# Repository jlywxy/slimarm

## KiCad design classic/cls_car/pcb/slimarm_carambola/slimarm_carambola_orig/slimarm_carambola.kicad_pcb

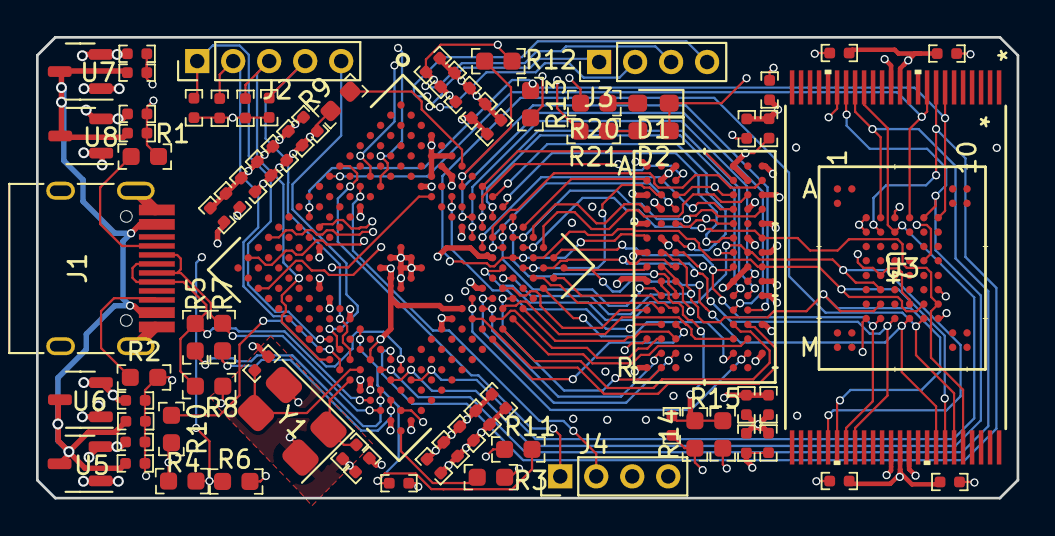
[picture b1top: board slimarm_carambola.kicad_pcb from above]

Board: 4 copper layers, 54.5 x 25.6 mm, 77 parts (0 on the bottom side), 84 nets.

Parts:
C1, C2, C3, C4, C5, C6, C7, C8, C9, C10, C11, C12, C13, C14, C15, C16, C17, C18, C19, C20, C21, C22, C23, C24, C25, C27, C28, C29, C30: 100nF; 0402
C26, C31, C32, C33, C34, C35, C36, C37, C38, C39, C40, C41: 22pF; 0402
D1, D2: LED; LED_0603_1608Metric_Pad1.05x0.95mm_HandSolder
J1: USB_C_Receptacle_USB2.0; USB_TYPEC_Receptacle
J2: Conn_01x05; PinHeader_1x05_P2.00mm_Vertical
J3, J4: Conn_01x04; PinHeader_1x04_P2.00mm_Vertical
R1, R2: 5.1k; 0603
R3: 6.8k; 0603
R4: NC; 0603
R5, R7: 39; 0603
R6: 0; 0603
R8, R10, R11, R14, R15: 1.5k; 0603
R9: 10k; 0603
R12, R13: 470k; 0603
R16, R17, R18, R19: 10k; 0402
R20, R21: 5.6k; 0603
U1: AT91SAM9G25-CU; AT91SAM9G25_JKT
U2: 16bit-DDR2-8bank-FBGA84; BGA84_DDR2
U3: 8bit-NAND-1CE-VFBGA63; VFBGA63_NAND
U4: 8bit-NAND-2CE-TSOP48; TSOP48_NAND
U5, U6, U7, U8: XC6206PxxxMR; SOT-23-3
Y1: Crystal_GND24; Crystal_5032-4P

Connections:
+5V: C33.2, C35.2, C37.2, C39.2, J1.A4 (VBUS), J1.A9 (VBUS), J1.B4 (VBUS), J1.B9 (VBUS), U5.3 (VI), U6.3 (VI), U7.3 (VI), U8.3 (VI)
/1v0_CPUCORE: C12.2, C13.2, C14.2, C15.2, C16.2, C17.2, C18.2, C40.2, U1.H14 (VDDCORE), U1.K8 (VDDCORE), U1.K9 (VDDCORE), U1.R12 (VDDPLLA), U1.T17 (VDDUTMIC), U8.2 (VO)
/1v8_CPUMEM: C9.2, C10.2, C11.2, C36.2, U1.D10 (VDDIOM), U1.D13 (VDDIOM), U1.F14 (VDDIOM), U6.2 (VO)
/1v8_DDR: C19.2, C20.2, C21.2, C22.2, C23.2, C24.2, C25.2, C38.2, U2.A1 (VDD), U2.A9 (VDDQ), U2.C1 (VDDQ), U2.C3 (VDDQ), U2.C7 (VDDQ), U2.C9 (VDDQ), U2.E1 (VDD), U2.E9 (VDDQ), U2.G1 (VDDQ), U2.G3 (VDDQ), U2.G7 (VDDQ), U2.G9 (VDDQ), U2.J1 (VDD), U2.J9 (VDD), U2.M9 (VDD), U2.R1 (VDD), U7.2 (VO)
/3v3: C1.2, C2.2, C3.2, C4.2, C5.2, C6.2, C7.2, C8.2, C27.2, C28.2, C29.2, C30.2, C34.2, J4.3, R4.1, R9.2, R10.2, R11.1, R12.2, R13.2, R15.2, R16.2, R17.2, R18.2, R19.2, U1.A4 (ADVREF), U1.A6 (XIN32), U1.B5 (VDDBU), U1.C6 (VDDANA), U1.H4 (VDDIOP1), U1.J14 (VDDNF), U1.K14 (VDDNF), U1.P7 (VDDIOP0), U1.P9 (BMS), U1.T13 (VDDOSC), U1.U16 (VDDUTMII), U3.C3 (WP#), U3.D3 (VCC2), U3.G4 (VCC2), U3.H8 (VCC), U3.J6 (VCC), U4.12 (Vcc), U4.19 (WP-), U4.37 (Vcc), U5.2 (VO)
/DDR_A0: U1.H15 (A2), U2.M8 (A0)
/DDR_A1: U1.H17 (A3), U2.M3 (A1)
/DDR_A2: U1.G17 (A4), U2.M7 (A2)
/DDR_A3: U1.G16 (A5), U2.N2 (A3)
/DDR_A4: U1.F17 (A6), U2.N8 (A4)
/DDR_A5: U1.E17 (A7), U2.N3 (A5)
/DDR_A6: U1.F16 (A8), U2.N7 (A6)
/DDR_A7: U1.G15 (A9), U2.P2 (A7)
/DDR_A8: U1.G14 (A10), U2.P8 (A8)
/DDR_A9: U1.F15 (A11), U2.P3 (A9)
/DDR_A10: U1.C8 (SDA10), U2.M2 (A10/AP)
/DDR_A11: U1.C17 (A13), U2.P7 (A11)
/DDR_A12: U1.E16 (A14), U2.R2 (A12)
/DDR_BA0: U1.C16 (A16), U2.L2 (BA0)
/DDR_BA1: U1.B17 (A17), U2.L3 (BA1)
/DDR_BA2: U1.E15 (A18), U2.L1 (BA2)
/DDR_CAS: U1.C10 (CAS), U2.L7 (CAS*)
/DDR_CKE: U1.B12 (SDCKE), U2.K2 (DKE)
/DDR_CLK: U1.D11 (SDCK), U2.J8 (CK)
/DDR_CS: R12.1, U1.B8 (NCS1), U2.L8 (CS*)
/DDR_D0: U1.D14 (D0), U2.G8 (DQ0), U3.H4 (I/O0), U4.29 (I/O0)
/DDR_D1: U1.D15 (D1), U2.G2 (DQ1), U3.J4 (I/O1), U4.30 (I/O1)
/DDR_D2: U1.A16 (D2), U2.H7 (DQ2), U3.K4 (I/O2), U4.31 (I/O2)
/DDR_D3: U1.B16 (D3), U2.H3 (DQ3), U3.K5 (I/O3), U4.32 (I/O3)
/DDR_D4: U1.A17 (D4), U2.H1 (DQ4), U3.K6 (I/O4), U4.41 (I/O4)
/DDR_D5: U1.B15 (D5), U2.H9 (DQ5), U3.J7 (I/O5), U4.42 (I/O5)
/DDR_D6: U1.C14 (D6), U2.F1 (DQ6), U3.K7 (I/O6), U4.43 (I/O6)
/DDR_D7: U1.B14 (D7), U2.F9 (DQ7), U3.J8 (I/O7), U4.44 (I/O7)
/DDR_D8: U1.A15 (D8), U2.C8 (DQ8)
/DDR_D9: U1.C15 (D9), U2.C2 (DQ9)
/DDR_D10: U1.D12 (D10), U2.D7 (DQ10)
/DDR_D11: U1.C13 (D11), U2.D3 (DQ11)
/DDR_D12: U1.A14 (D12), U2.D1 (DQ12)
/DDR_D13: U1.B13 (D13), U2.D9 (DQ13)
/DDR_D14: U1.A13 (D14), U2.B1 (DQ14)
/DDR_D15: U1.C12 (D15), U2.B9 (DQ15)
/DDR_DQM0: U1.A10 (DQM0), U2.F3 (LDM)
/DDR_DQM1: U1.B10 (DQM1), U2.B3 (UDM)
/DDR_DQS0: U1.A11 (DQS0), U2.F7 (LDQS)
/DDR_DQS1: U1.A9 (DQS1), U2.B7 (UDQS)
/DDR_NCLK: U1.C11 (*SDCK), U2.K8 (CK*)
/DDR_RAS: U1.B11 (RAS), U2.K7 (RAS*)
/DDR_WE: U1.A12 (SDWE), U2.K3 (WE*)
/DEBUG_RXD: J3.2, U1.U3 (PA9)
/DEBUG_TXD: J3.1, U1.T1 (PA10)
/DN: J1.A7 (D-), J1.B7 (D-), R7.2, U1.U15 (HHSDMA)
/DP: J1.A6 (D+), J1.B6 (D+), R5.2, R8.2, U1.U14 (HHSDPA)
/JTAG_RST: J2.4, R18.1, U1.T11 (NTRST)
/JTAG_TCK: J2.3, R19.1, U1.U10 (TCK)
/JTAG_TDI: J2.1, R16.1, U1.T9 (TDI)
/JTAG_TDO: J2.5, U1.T10 (TDO)
/JTAG_TMS: J2.2, R17.1, U1.U11 (TMS)
/NAND_ALE: U1.R13 (PD2), U3.C4 (ALE), U4.17 (ALE)
/NAND_CLE: U1.P15 (PD3), U3.D5 (CLE), U4.16 (CLE)
/NAND_CS: U1.H1 (PC14), U3.C6 (CE#), U4.9 (CE-)
/NAND_OE: U1.P13 (PD0), U3.D4 (RE#), U4.8 (RE-)
/NAND_RNB: R13.1, U1.L2 (PC13), U3.C8 (R/B#), U4.7 (R/B-)
/NAND_WE: U1.R14 (PD1), U3.C7 (WE#), U4.18 (WE-)
/UART_RXD: J3.4, U1.P1 (PA1)
/UART_TXD: J3.3, U1.L3 (PA0)
/UART_URXD: J4.2, U1.G3 (PC9)
/UART_UTXD: J4.1, U1.G1 (PC8)
/USBD_FS_DN: R7.1, U1.T15 (HFSDMA)
/USBD_FS_DP: R5.1, U1.T14 (HFSDPA)
/XTAL_IN: C32.1, U1.T12 (XIN), Y1.3
/XTAL_OUT: C31.2, U1.U12 (XOUT), Y1.1
GND: C1.1, C2.1, C3.1, C4.1, C5.1, C6.1, C7.1, C8.1, C9.1, C10.1, C11.1, C12.1, C13.1, C14.1, C15.1, C16.1, C17.1, C18.1, C19.1, C20.1, C21.1, C22.1, C23.1, C24.1, C25.1, C26.1, C27.1, C28.1, C29.1, C30.1, C31.1, C32.2, C33.1, C34.1, C35.1, C36.1, C37.1, C38.1, C39.1, C40.1, C41.1, D1.1 (K), D2.1 (K), J1.A1 (GND), J1.A12 (GND), J1.B1 (GND), J1.B12 (GND), J1.S1 (SHIELD), J4.4, R1.2, R2.2, R3.1, R6.2, R14.1, U1.B6 (GNDBU), U1.B7 (TST), U1.D6 (GNDANA), U1.H8 (GNDCORE), U1.H9 (GNDIOM), U1.H10 (GNDIOM), U1.J8 (GNDCORE), U1.J9 (GNDIOM), U1.J10 (GNDIOM), U1.K10 (GNDCORE), U1.M4 (GNDIOP), U1.P6 (GNDIOP), U1.T16 (GNDUTMI), U1.U13 (GNDOSC), U2.A3 (VSS), U2.A7 (VSSQ), U2.B2 (VSSQ), U2.B8 (VSSQ), U2.D2 (VSSQ), U2.D8 (VSSQ), U2.E3 (VSS), U2.E7 (VSSQ), U2.F2 (VSSQ), U2.F8 (VSSQ), U2.H2 (VSSQ), U2.H8 (VSSQ), U2.J3 (VSS), U2.J7 (VSS), U2.K9 (ODT), U2.N1 (VSS), U2.P9 (VSS), U3.C5 (VSS), U3.F7 (VSS2), U3.K3 (VSS), U3.K8 (VSS), U4.13 (Vss), U4.36 (Vss), U4.38 (PRE/VSS), U5.1 (GND), U6.1 (GND), U7.1 (GND), U8.1 (GND), Y1.2, Y1.4
unnamed: D1.2 (A), R20.1
unnamed: D2.2 (A), R21.1
unnamed: J1.A5 (CC1), R1.1
unnamed: J1.B5 (CC2), R2.1
unnamed: R4.2, R6.1, U1.D7 (JTAGSEL)
unnamed: R20.2, U1.F4 (PC1)
unnamed: R21.2, U1.F3 (PC2)
unnamed: R9.1, U1.A7 (WKUP)
unnamed: C41.2, R11.2, U1.P10 (NRST)
unnamed: R10.1, U1.P14 (PD5)
unnamed: R3.2, U1.U17 (VBG)
unnamed: C26.2, R14.2, R15.1, U2.J2 (VREF)

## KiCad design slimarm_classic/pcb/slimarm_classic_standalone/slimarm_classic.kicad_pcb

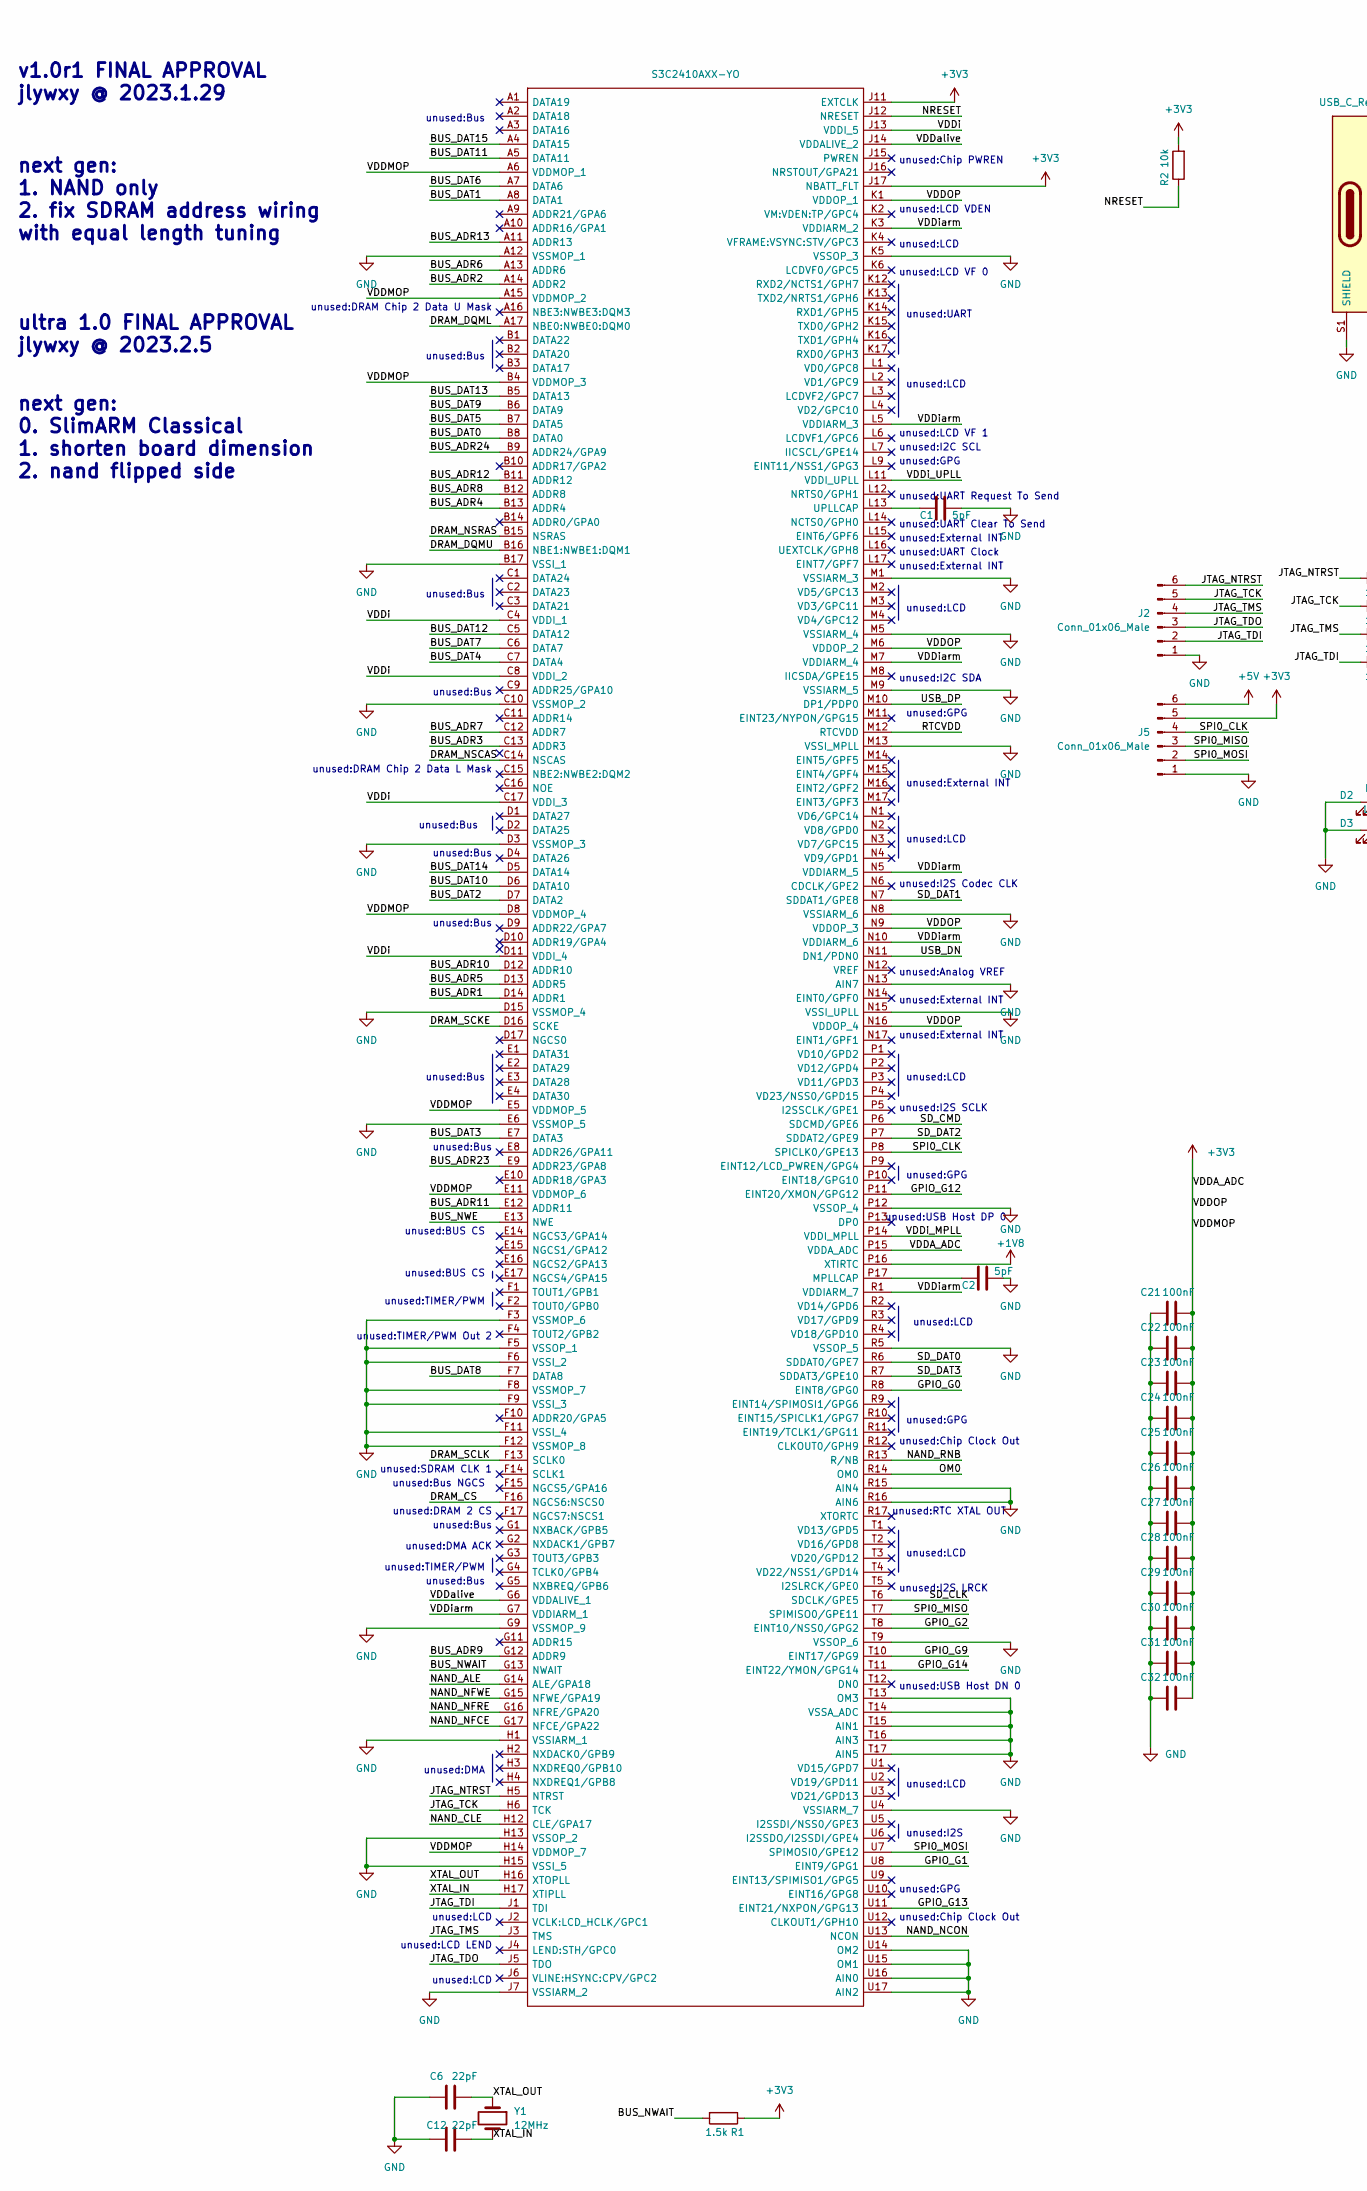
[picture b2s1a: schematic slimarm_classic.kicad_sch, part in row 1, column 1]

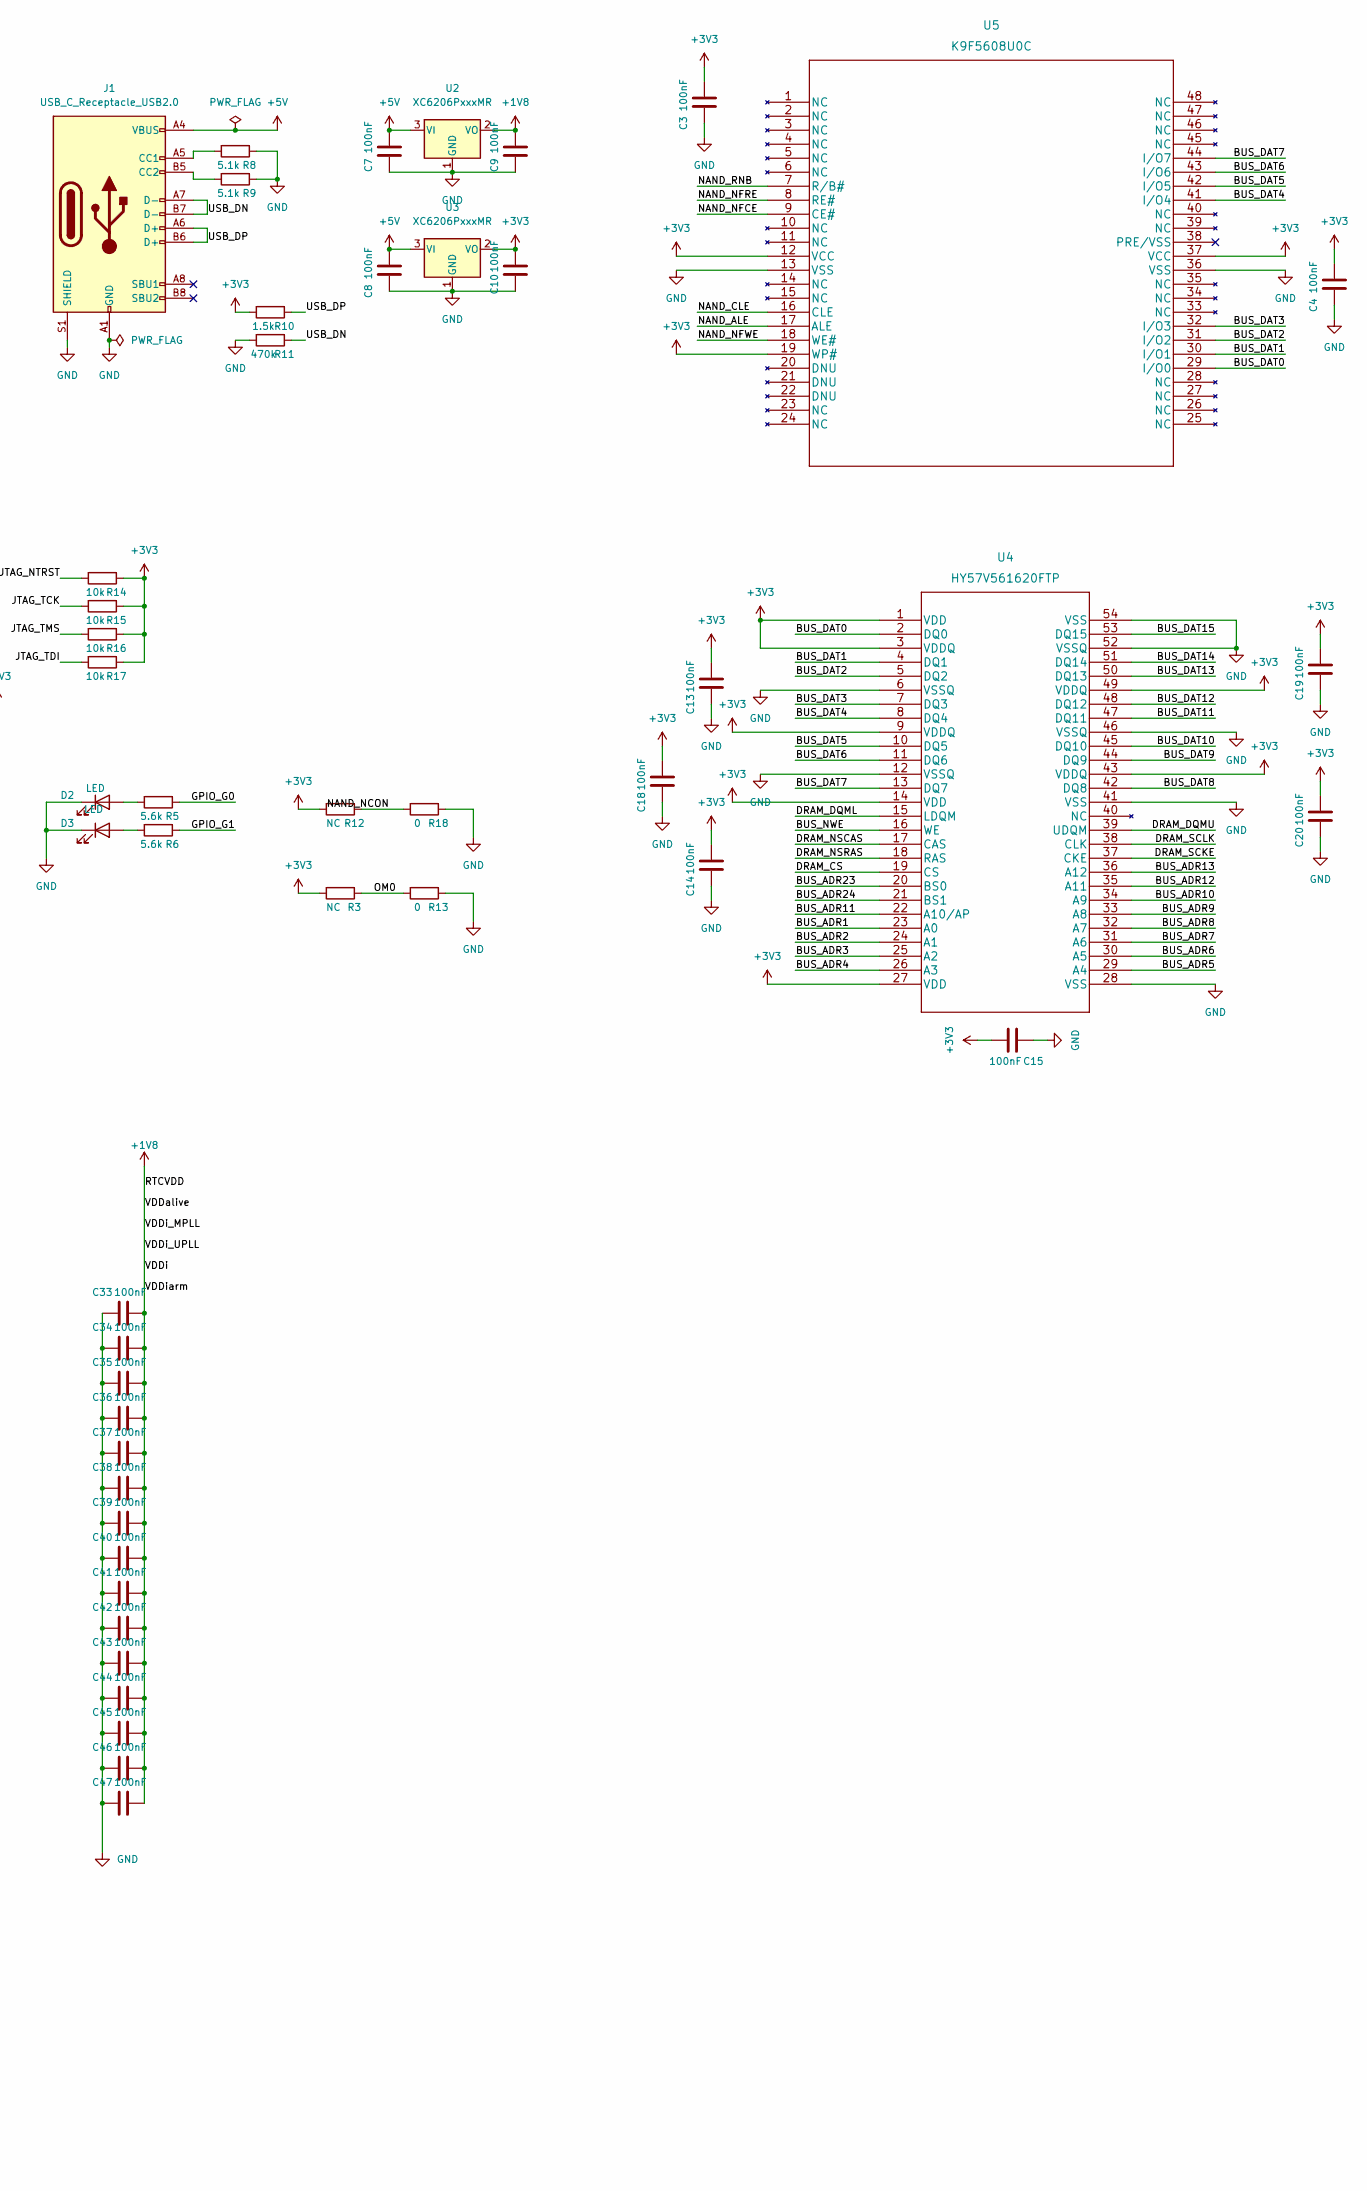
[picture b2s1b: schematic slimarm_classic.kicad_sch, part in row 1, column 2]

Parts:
C1, C2: 5pF; C_0402_1005Metric_Pad0.74x0.62mm_HandSolder
C3, C4, C7, C8, C9, C10, C13, C14, C15, C18, C19, C20, C21, C22, C23, C24, C25, C26, C27, C28, C29, C30, C31, C32, C33, C34, C35, C36, C37, C38, C39, C40, C41, C42, C43, C44, C45, C46, C47: 100nF; C_0402_1005Metric_Pad0.74x0.62mm_HandSolder
C6, C12: 22pF; C_0402_1005Metric_Pad0.74x0.62mm_HandSolder
D2, D3: LED; LED_0603_1608Metric_Pad1.05x0.95mm_HandSolder
IC1: S3C2410AXX-YO; BGA272C80P17X17_1400X1400X116; Manufacturer_Part_Number S3C2410AXX-YO
J1: USB_C_Receptacle_USB2.0; USB_C_Receptacle_HRO_TYPE-C-31-M-12
J2, J5: Conn_01x06_Male; PinSocket_2x03_P2.00mm_Vertical_SMD
R1, R10: 1.5k; R_0603_1608Metric_Pad0.98x0.95mm_HandSolder
R2, R14, R15, R16, R17: 10k; R_0603_1608Metric_Pad0.98x0.95mm_HandSolder
R3, R12: NC; R_0603_1608Metric_Pad0.98x0.95mm_HandSolder
R5, R6: 5.6k; R_0603_1608Metric_Pad0.98x0.95mm_HandSolder
R8, R9: 5.1k; R_0603_1608Metric_Pad0.98x0.95mm_HandSolder
R11: 470k; R_0603_1608Metric_Pad0.98x0.95mm_HandSolder
R13, R18: 0; R_0603_1608Metric_Pad0.98x0.95mm_HandSolder
U2, U3: XC6206PxxxMR; SOT-23
U4: HY57V561620FTP
U5: K9F5608U0C; M29W640FB70N6E
Y1: 12MHz; Crystal_SMD_5032-2Pin_5.0x3.2mm

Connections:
+1V8: C9.2, C33.2, C34.2, C35.2, C36.2, C37.2, C38.2, C39.2, C40.2, C41.2, C42.2, C43.2, C44.2, C45.2, C46.2, C47.2, IC1.C4 (VDDI_1), IC1.C8 (VDDI_2), IC1.C17 (VDDI_3), IC1.D11 (VDDI_4), IC1.G6 (VDDALIVE_1), IC1.G7 (VDDIARM_1), IC1.J13 (VDDI_5), IC1.J14 (VDDALIVE_2), IC1.K3 (VDDIARM_2), IC1.L5 (VDDIARM_3), IC1.L11 (VDDI_UPLL), IC1.M7 (VDDIARM_4), IC1.M12 (RTCVDD), IC1.N5 (VDDIARM_5), IC1.N10 (VDDIARM_6), IC1.P14 (VDDI_MPLL), IC1.P16 (XTIRTC), IC1.R1 (VDDIARM_7), U2.2 (VO)
+3V3: C3.2, C4.2, C10.2, C13.2, C14.2, C15.2, C18.2, C19.2, C20.2, C21.2, C22.2, C23.2, C24.2, C25.2, C26.2, C27.2, C28.2, C29.2, C30.2, C31.2, C32.2, IC1.A6 (VDDMOP_1), IC1.A15 (VDDMOP_2), IC1.B4 (VDDMOP_3), IC1.D8 (VDDMOP_4), IC1.E5 (VDDMOP_5), IC1.E11 (VDDMOP_6), IC1.H14 (VDDMOP_7), IC1.J11 (EXTCLK), IC1.J17 (NBATT_FLT), IC1.K1 (VDDOP_1), IC1.M6 (VDDOP_2), IC1.N9 (VDDOP_3), IC1.N16 (VDDOP_4), IC1.P15 (VDDA_ADC), J5.5, R1.1, R2.2, R3.2, R10.2, R12.2, R14.1, R15.1, R16.1, R17.1, U3.2 (VO), U4.1 (VDD), U4.3 (VDDQ), U4.9 (VDDQ), U4.14 (VDD), U4.27 (VDD), U4.43 (VDDQ), U4.49 (VDDQ), U5.12 (VCC), U5.19 (WP#), U5.37 (VCC)
+5V: C7.2, C8.2, J1.A4 (VBUS), J1.A9 (VBUS), J1.B4 (VBUS), J1.B9 (VBUS), J5.6, U2.3 (VI), U3.3 (VI)
/BUS_ADR1: IC1.D14 (ADDR1), U4.23 (A0)
/BUS_ADR2: IC1.A14 (ADDR2), U4.24 (A1)
/BUS_ADR3: IC1.C13 (ADDR3), U4.25 (A2)
/BUS_ADR4: IC1.B13 (ADDR4), U4.26 (A3)
/BUS_ADR5: IC1.D13 (ADDR5), U4.29 (A4)
/BUS_ADR6: IC1.A13 (ADDR6), U4.30 (A5)
/BUS_ADR7: IC1.C12 (ADDR7), U4.31 (A6)
/BUS_ADR8: IC1.B12 (ADDR8), U4.32 (A7)
/BUS_ADR9: IC1.G12 (ADDR9), U4.33 (A8)
/BUS_ADR10: IC1.D12 (ADDR10), U4.34 (A9)
/BUS_ADR11: IC1.E12 (ADDR11), U4.22 (A10/AP)
/BUS_ADR12: IC1.B11 (ADDR12), U4.35 (A11)
/BUS_ADR13: IC1.A11 (ADDR13), U4.36 (A12)
/BUS_ADR23: IC1.E9 (ADDR23/GPA8), U4.20 (BS0)
/BUS_ADR24: IC1.B9 (ADDR24/GPA9), U4.21 (BS1)
/BUS_DAT0: IC1.B8 (DATA0), U4.2 (DQ0), U5.29 (I/O0)
/BUS_DAT1: IC1.A8 (DATA1), U4.4 (DQ1), U5.30 (I/O1)
/BUS_DAT2: IC1.D7 (DATA2), U4.5 (DQ2), U5.31 (I/O2)
/BUS_DAT3: IC1.E7 (DATA3), U4.7 (DQ3), U5.32 (I/O3)
/BUS_DAT4: IC1.C7 (DATA4), U4.8 (DQ4), U5.41 (I/O4)
/BUS_DAT5: IC1.B7 (DATA5), U4.10 (DQ5), U5.42 (I/O5)
/BUS_DAT6: IC1.A7 (DATA6), U4.11 (DQ6), U5.43 (I/O6)
/BUS_DAT7: IC1.C6 (DATA7), U4.13 (DQ7), U5.44 (I/O7)
/BUS_DAT8: IC1.F7 (DATA8), U4.42 (DQ8)
/BUS_DAT9: IC1.B6 (DATA9), U4.44 (DQ9)
/BUS_DAT10: IC1.D6 (DATA10), U4.45 (DQ10)
/BUS_DAT11: IC1.A5 (DATA11), U4.47 (DQ11)
/BUS_DAT12: IC1.C5 (DATA12), U4.48 (DQ12)
/BUS_DAT13: IC1.B5 (DATA13), U4.50 (DQ13)
/BUS_DAT14: IC1.D5 (DATA14), U4.51 (DQ14)
/BUS_DAT15: IC1.A4 (DATA15), U4.53 (DQ15)
/BUS_NWAIT: IC1.G13 (NWAIT), R1.2
/BUS_NWE: IC1.E13 (NWE), U4.16 (WE)
/DRAM_CS: IC1.F16 (NGCS6:NSCS0), U4.19 (CS)
/DRAM_DQML: IC1.A17 (NBE0:NWBE0:DQM0), U4.15 (LDQM)
/DRAM_DQMU: IC1.B16 (NBE1:NWBE1:DQM1), U4.39 (UDQM)
/DRAM_NSCAS: IC1.C14 (NSCAS), U4.17 (CAS)
/DRAM_NSRAS: IC1.B15 (NSRAS), U4.18 (RAS)
/DRAM_SCKE: IC1.D16 (SCKE), U4.37 (CKE)
/DRAM_SCLK: IC1.F13 (SCLK0), U4.38 (CLK)
/GPIO_G0: IC1.R8 (EINT8/GPG0), R5.1
/GPIO_G1: IC1.U8 (EINT9/GPG1), R6.1
/GPIO_G2: IC1.T8 (EINT10/NSS0/GPG2)
/GPIO_G9: IC1.T10 (EINT17/GPG9)
/GPIO_G12: IC1.P11 (EINT20/XMON/GPG12)
/GPIO_G13: IC1.U11 (EINT21/NXPON/GPG13)
/GPIO_G14: IC1.T11 (EINT22/YMON/GPG14)
/JTAG_NTRST: IC1.H5 (NTRST), J2.6, R14.2
/JTAG_TCK: IC1.H6 (TCK), J2.5, R15.2
/JTAG_TDI: IC1.J1 (TDI), J2.2, R17.2
/JTAG_TDO: IC1.J5 (TDO), J2.3
/JTAG_TMS: IC1.J3 (TMS), J2.4, R16.2
/NAND_ALE: IC1.G14 (ALE/GPA18), U5.17 (ALE)
/NAND_CLE: IC1.H12 (CLE/GPA17), U5.16 (CLE)
/NAND_NCON: IC1.U13 (NCON), R12.1, R18.2
/NAND_NFCE: IC1.G17 (NFCE/GPA22), U5.9 (CE#)
/NAND_NFRE: IC1.G16 (NFRE/GPA20), U5.8 (RE#)
/NAND_NFWE: IC1.G15 (NFWE/GPA19), U5.18 (WE#)
/NAND_RNB: IC1.R13 (R/NB), U5.7 (R/B#)
/NRESET: IC1.J12 (NRESET), R2.1
/OM0: IC1.R14 (OM0), R3.1, R13.2
/SD_CLK: IC1.T6 (SDCLK/GPE5)
/SD_CMD: IC1.P6 (SDCMD/GPE6)
/SD_DAT0: IC1.R6 (SDDAT0/GPE7)
/SD_DAT1: IC1.N7 (SDDAT1/GPE8)
/SD_DAT2: IC1.P7 (SDDAT2/GPE9)
/SD_DAT3: IC1.R7 (SDDAT3/GPE10)
/SPI0_CLK: IC1.P8 (SPICLK0/GPE13), J5.4
/SPI0_MISO: IC1.T7 (SPIMISO0/GPE11), J5.3
/SPI0_MOSI: IC1.U7 (SPIMOSI0/GPE12), J5.2
/USB_DN: IC1.N11 (DN1/PDN0), J1.A7 (D-), J1.B7 (D-), R11.1
/USB_DP: IC1.M10 (DP1/PDP0), J1.A6 (D+), J1.B6 (D+), R10.1
/XTAL_IN: C12.2, IC1.H17 (XTIPLL), Y1.2
/XTAL_OUT: C6.2, IC1.H16 (XTOPLL), Y1.1
GND: C1.2, C2.2, C3.1, C4.1, C6.1, C7.1, C8.1, C9.1, C10.1, C12.1, C13.1, C14.1, C15.1, C18.1, C19.1, C20.1, C21.1, C22.1, C23.1, C24.1, C25.1, C26.1, C27.1, C28.1, C29.1, C30.1, C31.1, C32.1, C33.1, C34.1, C35.1, C36.1, C37.1, C38.1, C39.1, C40.1, C41.1, C42.1, C43.1, C44.1, C45.1, C46.1, C47.1, D2.1 (K), D3.1 (K), IC1.A12 (VSSMOP_1), IC1.B17 (VSSI_1), IC1.C10 (VSSMOP_2), IC1.D3 (VSSMOP_3), IC1.D15 (VSSMOP_4), IC1.E6 (VSSMOP_5), IC1.F3 (VSSMOP_6), IC1.F5 (VSSOP_1), IC1.F6 (VSSI_2), IC1.F8 (VSSMOP_7), IC1.F9 (VSSI_3), IC1.F11 (VSSI_4), IC1.F12 (VSSMOP_8), IC1.G9 (VSSMOP_9), IC1.H1 (VSSIARM_1), IC1.H13 (VSSOP_2), IC1.H15 (VSSI_5), IC1.J7 (VSSIARM_2), IC1.K5 (VSSOP_3), IC1.M1 (VSSIARM_3), IC1.M5 (VSSIARM_4), IC1.M9 (VSSIARM_5), IC1.M13 (VSSI_MPLL), IC1.N8 (VSSIARM_6), IC1.N13 (AIN7), IC1.N15 (VSSI_UPLL), IC1.P12 (VSSOP_4), IC1.R5 (VSSOP_5), IC1.R15 (AIN4), IC1.R16 (AIN6), IC1.T9 (VSSOP_6), IC1.T13 (OM3), IC1.T14 (VSSA_ADC), IC1.T15 (AIN1), IC1.T16 (AIN3), IC1.T17 (AIN5), IC1.U4 (VSSIARM_7), IC1.U14 (OM2), IC1.U15 (OM1), IC1.U16 (AIN0), IC1.U17 (AIN2), J1.A1 (GND), J1.A12 (GND), J1.B1 (GND), J1.B12 (GND), J1.S1 (SHIELD), J2.1, J5.1, R8.1, R9.1, R11.2, R13.1, R18.1, U2.1 (GND), U3.1 (GND), U4.6 (VSSQ), U4.12 (VSSQ), U4.28 (VSS), U4.41 (VSS), U4.46 (VSSQ), U4.52 (VSSQ), U4.54 (VSS), U5.13 (VSS), U5.36 (VSS)
unnamed: C1.1, IC1.L13 (UPLLCAP)
unnamed: C2.1, IC1.P17 (MPLLCAP)
unnamed: D2.2 (A), R5.2
unnamed: D3.2 (A), R6.2
unnamed: J1.A5 (CC1), R8.2
unnamed: J1.B5 (CC2), R9.2

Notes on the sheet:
unused:DRAM Chip 2 Data U Mask
unused:DRAM Chip 2 Data L Mask
unused:Bus
unused:TIMER/PWM Out 2
unused:I2S LRCK
unused:LCD
unused:UART
unused:UART Clear To Send
unused:External INT
unused:DRAM 2 CS
unused:GPG
unused:RTC XTAL OUT
unused:LCD VF 0
unused:I2S
unused:Chip Clock Out
unused:USB Host DN 0
unused:LCD LEND
unused:LCD VF 1
unused:LCD VDEN
unused:I2C SCL
unused:TIMER/PWM
unused:BUS CS
unused:Chip Clock Out
unused:I2S Codec CLK
unused:USB Host DP 0
unused:DMA ACK
unused:Chip PWREN
next gen: 0. SlimARM Classical 1. shorten board dimension 2. nand flipped side
unused:UART Request To Send
ultra 1.0 FINAL APPROVAL jlywxy @ 2023.2.5
unused:Bus NGCS
unused:I2S SCLK
unused:SDRAM CLK 1
next gen: 1. NAND only 2. fix SDRAM address wiring with equal length tuning
unused:DMA
unused:I2C SDA
unused:UART Clock
unused:Analog VREF
v1.0r1 FINAL APPROVAL jlywxy @ 2023.1.29

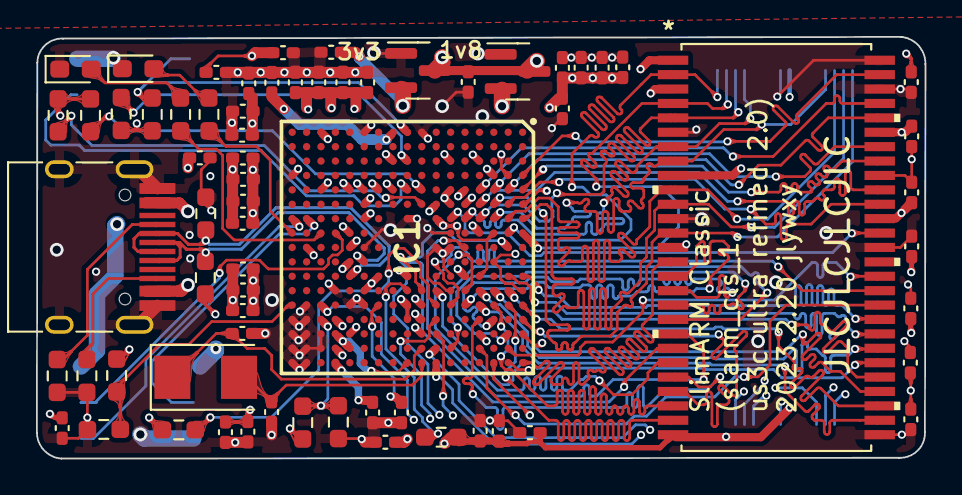
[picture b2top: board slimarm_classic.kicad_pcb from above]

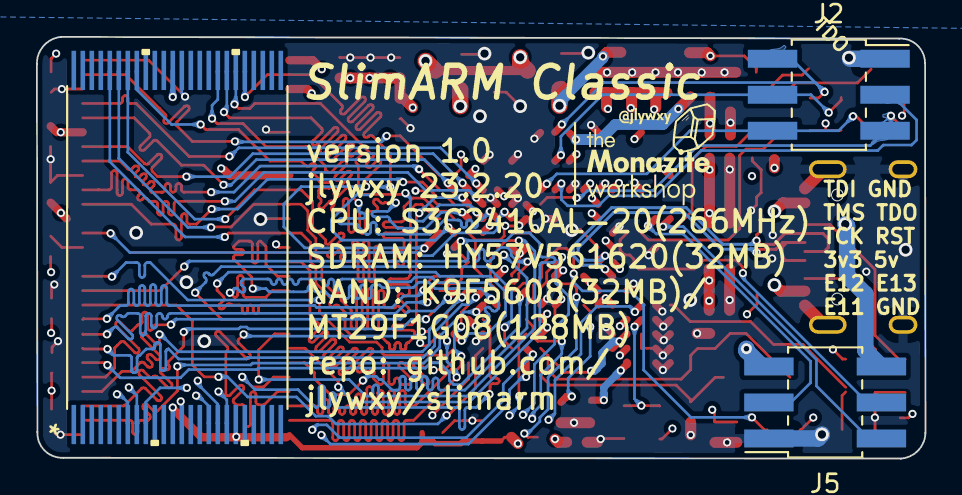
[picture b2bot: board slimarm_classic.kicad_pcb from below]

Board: 4 copper layers, 49.4 x 23.4 mm, 70 parts (3 on the bottom side), 73 nets.

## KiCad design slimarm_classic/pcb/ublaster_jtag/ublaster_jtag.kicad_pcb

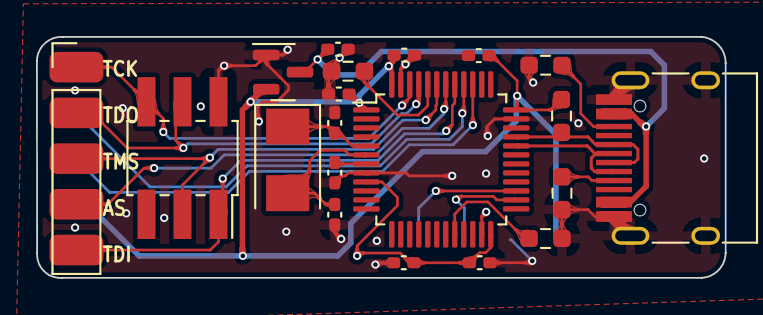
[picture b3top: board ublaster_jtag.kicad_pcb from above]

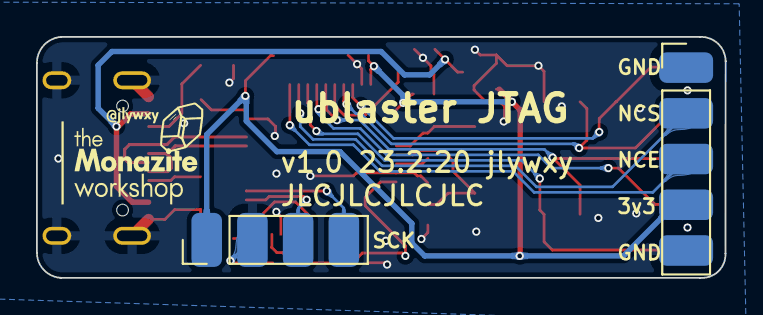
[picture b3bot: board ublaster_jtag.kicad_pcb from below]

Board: 2 copper layers, 38.3 x 13.4 mm, 22 parts (2 on the bottom side), 21 nets.

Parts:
C5, C11, C48, C49, C50, C51, C52: 100nF; C_0402_1005Metric_Pad0.74x0.62mm_HandSolder
C16, C17: 22pF; C_0402_1005Metric_Pad0.74x0.62mm_HandSolder
J3, J6: Conn_01x05; PinHeader_1x05_P2.54mm_Vertical
J4: USB_C_Receptacle_USB2.0; USB_C_Receptacle_HRO_TYPE-C-31-M-12
J7: Conn_01x04; PinHeader_1x04_P2.54mm_Vertical
J8: Conn_01x06_Male; PinSocket_2x03_P2.00mm_Vertical_SMD
R19, R20: 5.1k; R_0603_1608Metric_Pad0.98x0.95mm_HandSolder
R22, R23: 10k; R_0603_1608Metric_Pad0.98x0.95mm_HandSolder
R24: 1.5k; R_0603_1608Metric_Pad0.98x0.95mm_HandSolder
U1: STM32F103C8Tx; LQFP-48_7x7mm_P0.5mm
U6: XC6206PxxxMR; SOT-23
Y2: 8MHz; Crystal_SMD_5032-2Pin_5.0x3.2mm

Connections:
/JTAG_TCK: J3.1, J8.6, U1.46 (PB9)
/JTAG_TDI: J3.5, J8.1, U1.41 (PB5)
/JTAG_TDO: J3.2, J8.4, U1.45 (PB8)
/JTAG_TMS: J3.3, J8.3, U1.43 (PB7)
/SWCLK: J7.4, U1.27 (PB14)
/SWDIO: J7.3, U1.26 (PB13)
/UB_3v3: C11.2, C48.2, C50.2, C51.2, C52.2, J6.4, J7.1, R24.1, U1.1 (VBAT), U1.9 (VDDA), U1.24 (VDD), U1.36 (VDD), U1.48 (VDD), U6.2 (VO)
/UB_ASDO: J3.4, U1.42 (PB6)
/UB_ASNCE: J6.3, U1.39 (PB3)
/UB_ASNCS: J6.2, U1.40 (PB4)
/UB_USB_DN: J4.A7 (D-), J4.B7 (D-), U1.32 (PA11)
/UB_USB_DP: J4.A6 (D+), J4.B6 (D+), R24.2, U1.33 (PA12)
/UB_VBUS: C5.2, J4.A4 (VBUS), J4.A9 (VBUS), J4.B4 (VBUS), J4.B9 (VBUS), U6.3 (VI)
/UB_XTAL_IN: C17.2, U1.6 (PD1), Y2.2
/UB_XTAL_OUT: C16.2, U1.5 (PD0), Y2.1
GND: C5.1, C11.1, C16.1, C17.1, C48.1, C49.2, C50.1, C51.1, C52.1, J4.A1 (GND), J4.A12 (GND), J4.B1 (GND), J4.B12 (GND), J4.S1 (SHIELD), J6.1, J6.5, J7.2, J8.2, R19.1, R20.1, R22.2, R23.2, U1.8 (VSSA), U1.23 (VSS), U1.35 (VSS), U1.47 (VSS), U6.1 (GND)
unnamed: C49.1, U1.7 (NRST)
unnamed: J4.A5 (CC1), R19.2
unnamed: J4.B5 (CC2), R20.2
unnamed: R22.1, U1.20 (PB2)
unnamed: R23.1, U1.44 (BOOT0)

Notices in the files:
parts and their libraries:
Copyright 2021 Accelerated Designs. All rights reserved.
